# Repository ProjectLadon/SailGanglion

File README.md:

# SailGanglion
This is the brains of each sail. This covers the electronics, sensors, and software for each sail. The master branch is currently devoted to the subscale test vessel; future variants will get their own branches. 

## Required Design Properties
* Continuously controls the orientation of the tail of each wing in response to commands.
* Tail orientation commanded +/- 30 degrees of neutral
* Battery powered
* Uses rosserial over WiFi for all communications
* Subscribes to tail commands
* Publishes sail heading commands

## Electronic Hardware Components
* Adafruit Feather Huzzah ESP8266 (https://www.adafruit.com/product/2821)
* Hitec HS-82MG Servo (https://hitecrcd.com/products/servos/micro-and-mini-servos/analog-micro-and-mini-servos/hs-82mg/product)
* Sparkfun MPU-9250 Breakout (https://www.sparkfun.com/products/13762)

## Mechanical Design
The sail was designed in Fusion 360. There will be a link here...

## Libraries
* rosserial (https://github.com/ProjectLadon/rosserial_arduino_lib)
* Sparkfun MPU-9650 DMP library, modified for ESP compatibility (https://github.com/rupin/SparkFun_MPU-9250-DMP_Arduino_Library)

## Pinout
* I2C pins -- per standard (GPIO4 & GPIO5)
* Servo PWM -- GPIO2
* Foresail Select (pull down) -- GPIO14
* Mizzen Select (pull down) -- GPIO12
* Leave foresail and mizzen select pins floating for single-sail operation

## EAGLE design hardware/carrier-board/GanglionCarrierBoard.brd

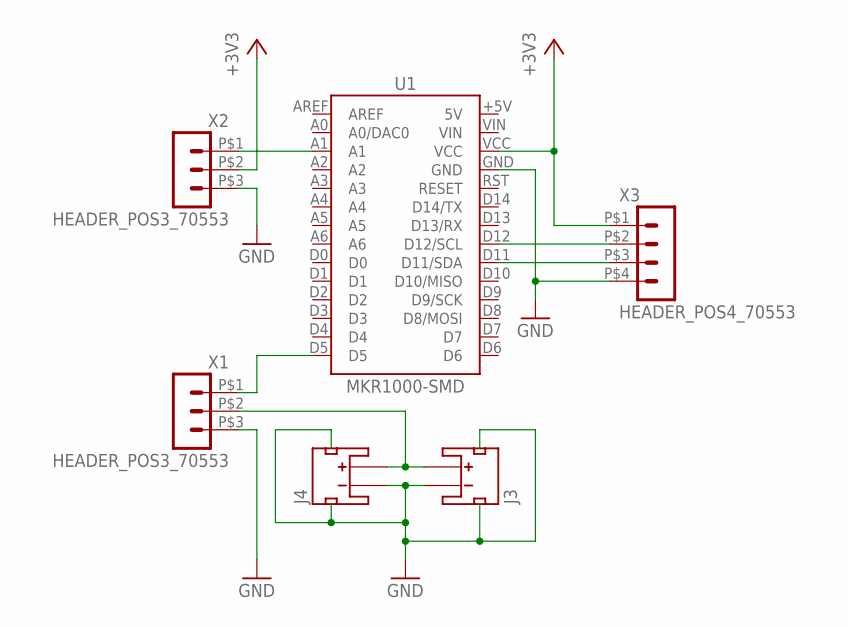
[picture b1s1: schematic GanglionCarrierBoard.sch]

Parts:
J3, J4: JST_2MM_MALE; JST-2-SMD
U1: MKR1000-SMD
X1, X2: HEADER_POS3_70553; 70553-POS3
X3: HEADER_POS4_70553; 70553-POS4

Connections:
+3V3: U1.VCC, X2.P$2 (2), X3.P$1 (1)
GND: J3.1 (-), J3.NC1 (PAD1), J3.NC2 (PAD2), J4.1 (-), J4.NC1 (PAD1), J4.NC2 (PAD2), U1.GND, X1.P$3 (3), X2.P$3 (3), X3.P$4 (4)
unnamed: U1.A1, X2.P$1 (1)
unnamed: U1.D5, X1.P$1 (1)
unnamed: J3.2 (+), J4.2 (+), X1.P$2 (2)
unnamed: U1.D12 (D12/SCL), X3.P$2 (2)
unnamed: U1.D11 (D11/SDA), X3.P$3 (3)

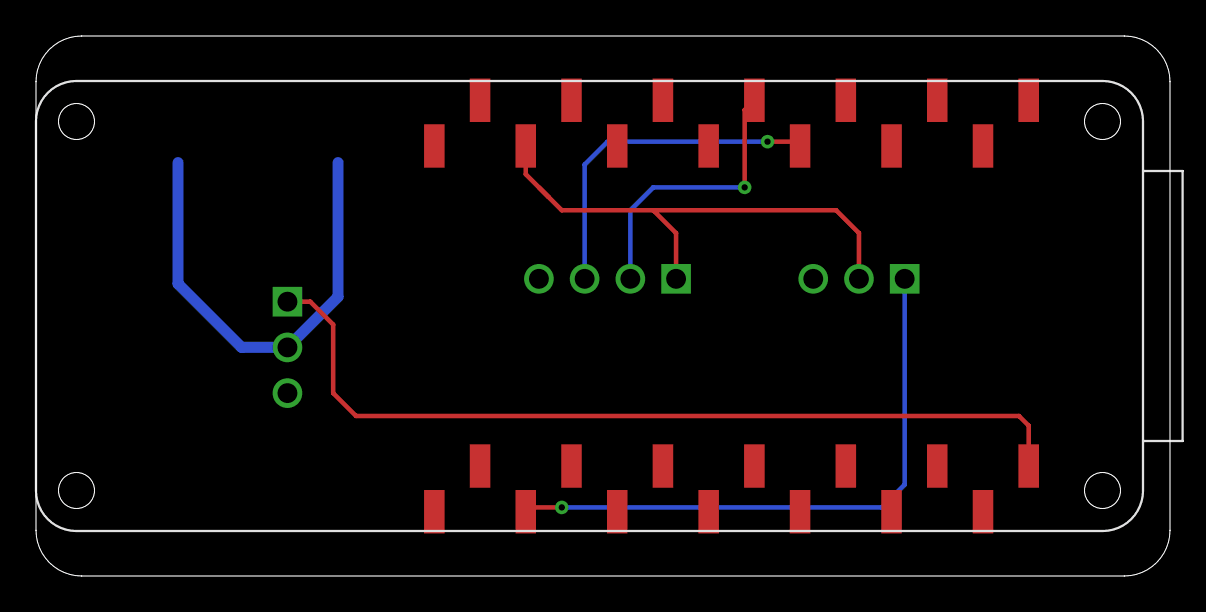
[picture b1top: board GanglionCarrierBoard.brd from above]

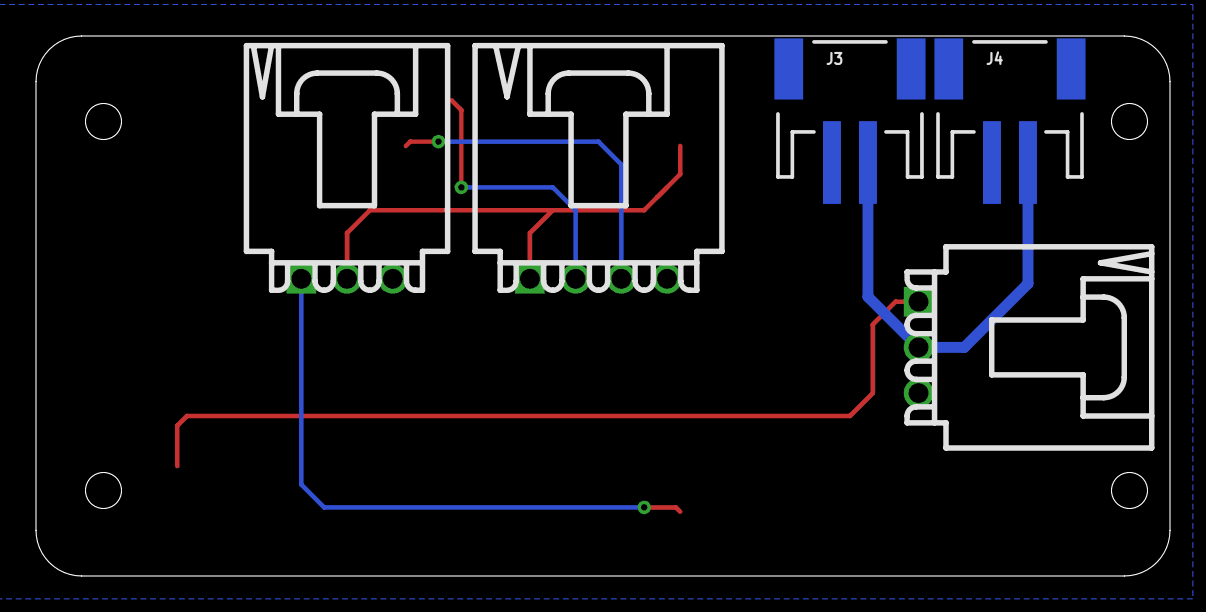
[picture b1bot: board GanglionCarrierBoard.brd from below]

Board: 2 copper layers, 63.0 x 30.0 mm, 6 parts (5 on the bottom side), 7 nets.

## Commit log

2017-08-29 Create the README
2017-08-29 Initial commit of code & datasheets
2017-08-29 Updated README.md
    Now with hardware links. Still don't have a great one for the AOA sensor, since that's custom.
2017-08-29 Added more design information to README
2017-09-01 Fixed and stable, still taking inputs in degrees. TODO: add input bounds checking
2017-09-02 Now working!
2017-09-28 Fixed excessively short delay on receive, added LED feedback and reconnection to wifi
2017-09-28 Added a timed demo for Makerfaire
2017-10-05 Added tail to list of exposed variables
2017-11-23 Working Software
2017-11-24 Added a design for the carrier board
2019-05-05 Updated to work with MPU9250, tested and working
2019-05-05 Ported over to ROS; yet to be tested
2019-05-05 Set ROS connection correctly
2019-09-22 Modified LadonSail for ESP8266 wifi, updated pinout. Note: Modified SparkFunMPU9250-DMP library for ESP compat. (see README.md)
2019-09-23 Corrected library in readme
2019-09-23 -- Added single sail operation configuration -- Fixed startup connection issue so it connects now -- Now crashes on ROS connection, but only if the rosserial is running
2019-09-29 Up to date with latest hardware changes.

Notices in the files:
parts and their libraries:
SparkFun-Connectors: Licensing: Creative Commons ShareAlike 4.0 International - https://creativecommons.org/licenses/by-sa/4.0
